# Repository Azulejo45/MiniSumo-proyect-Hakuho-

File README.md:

### ┍━━━━━━━━━━━━»•» 🌺 «•«━━━━┑
#   ┕MiniSumo-Project-Hakuho┙        

### - Proyecto de mini sumo con la capacidad de ser controlado de manera bluetooth y automata. Equipado con 4 sensores:  2 laterales, 1 frontal y uno en la parte inferior, el de piso.
♥

## ..••°°━✦❘༻⋞ 〈 Autores  〉 ⋟༺❘✦━━°°••..

- ⋆ˊˎ-   ┌──༺♥༻❀**Velazquez Joaquim**❀༺♥༻──┐
  
- ⋆ˊˎ-  ↻ ◁ I**Perez Sebastían**I ▷ ↺3:11 ───ㅇ──── 5:25

- ⋆ˊˎ-   》＊•̩̩͙✩•̩̩͙*˚**Demian Ramirez**˚*•̩̩͙✩•̩̩͙*˚《

### *---02/10/2025---*

♥
## •*¨*•.¸¸☆*･ﾟ Especificaciones generales ﾟ･*☆¸¸.•*¨*•

˚₊· ͟͟͞͞➳❥ Dimensiones del robot: 10 cm x 10 cm x 4,5 cm.

˚₊· ͟͟͞͞➳❥ Consumo total: 7,4V.

˚₊· ͟͟͞͞➳❥ Corriente total: 800mA.

˚₊· ͟͟͞͞➳❥ Material de la carrocería: PLA.

˚₊· ͟͟͞͞➳❥ Peso (aproximado): 250g.
## ✭∞∞∞∞∞∞∞∞✭∞∞•,¸,.·' ✩ '·.,¸,•∞∞✭∞∞∞∞∞∞∞∞✭

♥
### ✎  (❁ᴗ͈ˬᴗ͈) ༉‧ ♡*.✧
## Objetivo del proyecto
### ✩°｡𓂃𓏧︶︶︶︶︶︶︶︶┈୨•♡•୧┈︶︶︶︶︶︶︶𓂃𓏧｡°✩
_El objetivo principal de este proyecto es poner a prueba lo aprendido en el transcurso del ciclo educativo y poder aplicarlo en el ensamblaje y preparacion de un robot modelo Mini-Sumo para que se encuentre en condiciones en poder participar en una competencia.
El Mini-sumo está implementado con sensores los cuales lo ayudarán en la detección de obstaculos y/o de un mini-sumo enemigo, utilizando su rampa para contraatacar hasta expulsarlo de la zona de combate._
_Además, el robot consta con un modo "remote control" (RC), esto está implementado con el sistema de bluetooth y wi-fi integrado en el ESP32._
### ✩°｡𓂃𓏧⌒⌒⌒⌒⌒⌒⌒⌒┈୨•♡•୧┈⌒⌒⌒⌒⌒⌒⌒⌒𓂃𓏧｡°✩

♥
### ∘₊✧───∘₊✧───•-•⟮ ◆ ⟯•-•───✧₊∘───✧₊∘
## ˗ˏˋ ꒰ **Este proyecto fue realizado con algunos componentes en donde se puede llegan a encontrar:** ꒱ ˎˊ˗

- Micro: Esp32 S3 super mini.
 > Memoria: 512 KB SRAM, 4 MB Flash.Conectividad: Wi-Fi 802.11 b/g/n (2,4 GHz).\
 > Bluetooth 5.0 LE (Low Energy).\
 > Alimentación: Funciona a 3,3 V con entrada USB-C de 5 V.

- Bateria de Lipo.
 > Almacenamiento: 7,4V.\
 > 2 celdas (3,7V por celda)
  
- Sensor de piso: TCRT5000.
 > Voltaje de operación: 3.3V-5V.\
 > Dimensiones: 31 mm × 13 mm × 2 mm.\
 > Rango de detección: 30° más amplio.

- Sensor detector de obstáculos: AD-32.
 > Voltaje de operacion: 3V-5.5V.\
 > Cantidad de pines: 4.\
 > Distancia de deteccion: 5 a 20mm.
 
- Motores: Micro motores Pololu 250RPM.
 > Dimensiones: 26x10x12mm.\
 > Voltaje de operacion: 6V.\
 > Torque maximo: 333Nm (Newton - metro).

- Puente H: DRV8833.
 > Dimensiones: 4 mm × 18,1 mm × 21,1 mm.\
 > Voltaje de operacion: 2.7V-10.8V.\
 > Corriente máxima de salida: 1,5A.
 ### ∘₊✧───∘₊✧──────✧₊∘───✧₊∘

♥
## ╔══✬✩══╡˚✧Componentes utilizados✧˚╞══✩✬══╗
- ˋ°•*⁀.¸➸ *Esp32 S3 super mini.*
- ˋ°•*⁀.¸➸ *Bateria de Lipo.*
- ˋ°•*⁀.¸➸ *TCRT5000.*
- ˋ°•*⁀.¸➸ *AD-32.*
- ˋ°•*⁀.¸➸ *Micro motores Pololu 250RPM.*
- ˋ°•*⁀.¸➸ *DRV8833.*
## ╚═══*+:｡ . ｡:+*═══✮❁•°❀°•❁✮═══*+:｡ . ｡:+*═══╝
/
/
/
/
/
♥
# Diseño del circuito

## Descripcion del funcionamiento

El minisumo utiliza sus varios sensores para guiarse, con dos ubicados en los costados; otro en la parte frontal. Cuando un objeto entra en el rango del sensor frontal, el minisumo avanza hasta chocar contra dicho objeto. Esto siempre se cumple hasta que se quite la orden.\
Cuando uno de los sensores en los costados detectan algo cerca, se posiciona para estar de frente al objeto, retrocediendo y girando en direccion paralela a este.

♥

## Layout de PCB

# Pasos a seguir para armar el mini-sumo
## ˚*•̩̩͙✩•̩̩͙*˚＊˚*•̩̩͙✩•̩̩͙*˚＊˚*•̩̩͙✩•̩̩͙*˚＊˚*•̩̩͙✩•̩̩͙*˚＊˚*•̩̩͙✩•̩̩͙*˚

### Primero elistaremos las herramientas necesarias para llevar a cabo la placa.
-Un recipiente\
-Percloruro\
-Una agujereadora\
-Una placa de cobre\
-Papel fotografico\
-Tinta Tonel\
-Una impresora(Para imprimir el diseño PCB)
-Cable USB-C (Para cargar el codigo.)

 ### -|preparación de la placa:

1. Descargar el archivo de PCB de "HakuhoNII.kicad_pcb" (YO NO LO DESCARGO PORQUE YA LO TENGO XDDDD).
2. Imprimir el PCB en una hoja fotográfica (como lo son las hojas de revista) con tinta "tonel".
3. Proceda a planchar el PCB a la placa del lado del cobre.
4. Revisar que el diagrama del PCB se haya pegado correctamente retirando la hoja fotográfica y cualquier excendete de esta(Utilice agua para remover con facilidad el papel).
5. Sumergir la placa en un recipiente con percloruro.
6. Dejarlo descansar un tiempo(Resivar periodicamente el cobre de la placa)
7. Cuando el cobre se haya disuelto y solo quede el diseño, retirarlo con CUIDADO(Es un liquido corrosivo;dificil de quitar de la ropa).
8. Limiparlo la placa con agua para quitar el excedente de percloruro.

 ### -|Soldar los componentes en la placa ya hecha en el siguiente orden:
 
1. Puentes
2. Boton
3. Capacitores
4. Switch
5. Pineras
6. Borneras
7. regulador

 ### Medidas de seguridad.

-El percloruro es un tanto corrosivo, capáz de manchar con facilidad la ropa y otra prendas.\
-Cuando vaya a hacer agujeros en la placa, tiene que ser en una superficie solida. Es probable que la placa pueda salir dispara en una base dispareja o inquieta.\
-Mientra planche, este atento a no quemar completamente el papel. Podria causar un incendio.

### Tipo de soldadura/ensamble
Todos los componentes deben fijados a la placa mendiante "soldadura de ola", el cual se utiliza para componentes de orificio pasante(THT). Los componentes debe ser introducidos desde el lado de la placa lisa y sin diseño,para ser soldados en el cobre que se encuentra del otro lado.
En las pineras que estan direccionadas en horizontal, se debe colocar el ESP32(integrado).
En la pineras que se encuentran en vertical, el DRV8833.

### -|Carroceria

1. Descargar el modelo 3D de la carroceria.
2. Descargar un modelo 3D de dos braquets y 2 ruedas con un radio de 20mm.
3. Imprimir ambos archivos.
4. Comprar cuatro tornillos para tuerca M3, 6 tuercas M3 y 2 prisioneros M3.
5. Unir la carroseria con los braquets mediante 4 tornillos M3 y 4 tuercas M3.

### -|Codigo

El codigo establece las instrucciones que ejecutara el integrado para poder accionar y manejar al mini-sumo.\
este es bastante simple y considera los 4 sensores teniendo en cuenta que:

- No debe salir del tatami.
- Debe atacar y empujar al otro mini-sumo fuera del area.
- Esquivar al mini-sumo rival cuando se le de la orden.

#### -|Compilacion/Carga

Cuando la placa ya este monatada, se utilizara un cable USB tipo C para conectar el integrado(ESP32) a un ordenador. Mediante el programa [Arduino IDE](https://www.arduino.cc/en/software). Copie el codigo que se encuentra en este repositorio y pueguelo en el programa. En el apartado superior encontrara 4 botones.\
El primero es para verificar si el programa tiene errores\
El segundo es para subir el codigo al integrado\
El tercero no es importante para esto.\
El cuarto es para poder seleccionar la placa y el puerto\
En este ultimo, busque el siguiente modelo: ESP32_S3_SUPER_MINI, y seleccionelo. En caso de no encontrarlo, use el "ESP32 S3 DEV MODULE". Junto a eso, seleccione el puerto USB por el cual esta conectado a su ordenador(Se cuenta de izquierda a derecha).\
Ahora, verifique el codigo por el primero boton de la parte superior. Si marca algun error, copie el codigo entero de nuevo y vuelva a pegarlo./
Una vez verificada la funcionalidad del codigo, utilice el segundo boton presente para poder subir el codigo al integrado de la placa. Si hay alguno otro error durante este proceso, consulte internet.

#### -[Librerias
Para poner librerias, dirigase al lateral izquierdo de la interfaz de Arduino IDE, y seleccione el tercer boton(Que contiene un simbolo con libros).
En el buscador de esta nueva pagina, encuentre las siguientes librerias:
-AdaFruit_NeoPixel.h

#### -[Datasheets/Referencias
-[AD-32](Recursos/Datasheet AD-32.jpg)

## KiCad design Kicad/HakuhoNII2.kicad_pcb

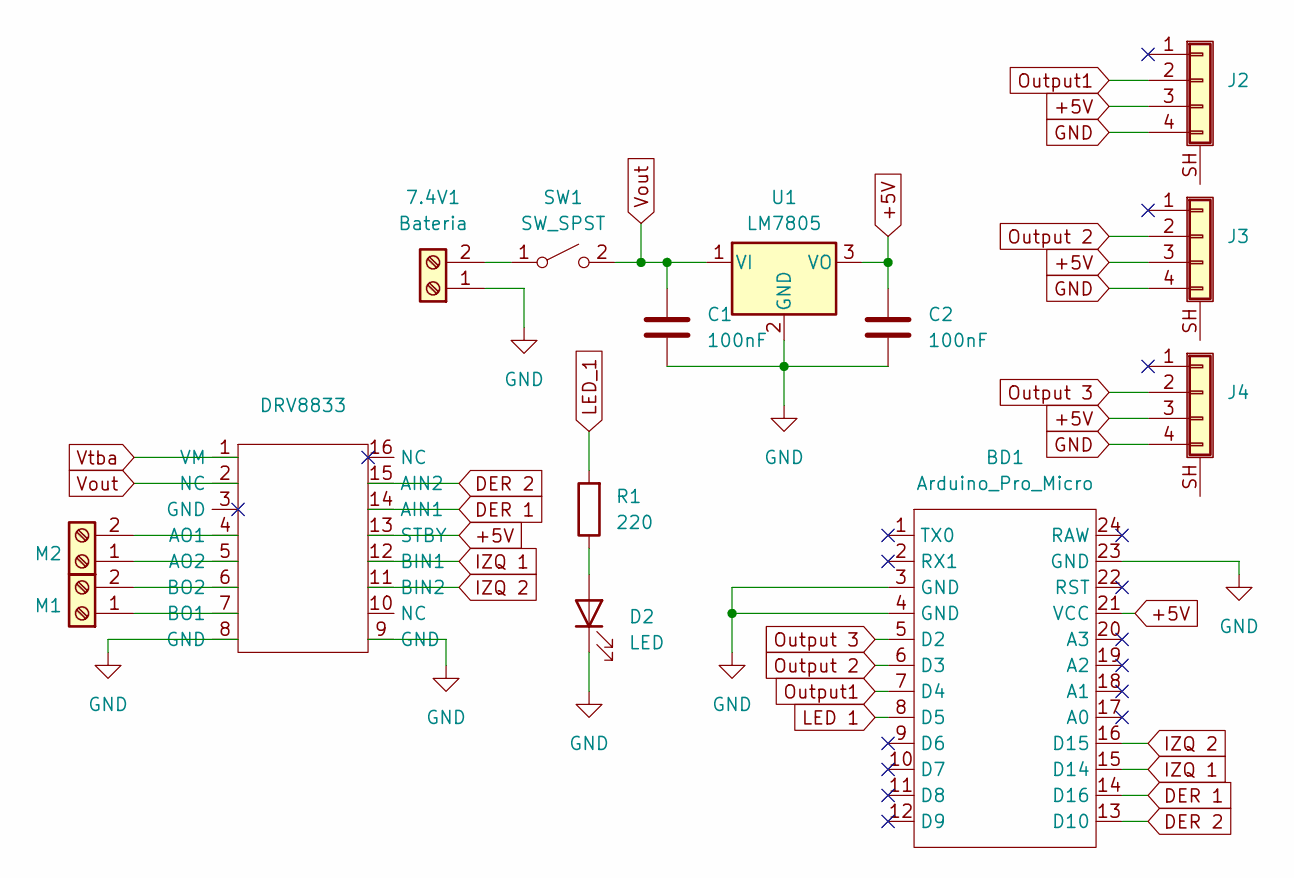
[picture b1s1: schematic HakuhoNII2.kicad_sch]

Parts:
7.4V1: Bateria; TerminalBlock_Phoenix_MKDS-1,5-2-5.08_1x02_P5.08mm_Horizont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
BD1: Arduino_Pro_Micro; Arduino PRO Micro
C1, C2: 100nF; C_Disc_D5.0mm_W2.5mm_P2.50mm
D2: LED; LED_D3.0mm_FlatTop
DRV8833: drv8833
J2, J3, J4: Conn_01x04_Shielded; PinHeader_1x04_P2.54mm_Vertical
M1, M2: Screw_Terminal_01x02; TerminalBlock_Phoenix_MKDS-1,5-2-5.08_1x02_P5.08mm_Horizont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
R1: 220; R_Axial_DIN0207_L6.3mm_D2.5mm_P7.62mm_Horizontal
SW1: SW_SPST; TerminalBlock_Phoenix_MKDS-1,5-2-5.08_1x02_P5.08mm_Horizont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
U1: LM7805; TO-220-3_Vertical

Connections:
+5V: BD1.21 (VCC), C2.1, DRV8833.13 (STBY), J2.3, J3.3, J4.3, U1.3 (VO)
DER 1: BD1.14 (D16), DRV8833.14 (AIN1)
DER 2: BD1.13 (D10), DRV8833.15 (AIN2)
GND: 7.4V1.1, BD1.3 (GND), BD1.4 (GND), BD1.23 (GND), C1.2, C2.2, D2.1 (K), DRV8833.8 (GND), DRV8833.9 (GND), J2.4, J3.4, J4.4, U1.2 (GND)
IZQ 1: BD1.15 (D14), DRV8833.12 (BIN1)
IZQ 2: BD1.16 (D15), DRV8833.11 (BIN2)
LED 1: BD1.8 (D5)
LED_1: R1.2
unnamed: 7.4V1.2, SW1.1 (A)
unnamed: D2.2 (A), R1.1
unnamed: DRV8833.4 (AO1), M2.2
unnamed: DRV8833.5 (AO2), M2.1
unnamed: DRV8833.7 (BO1), M1.1
unnamed: DRV8833.6 (BO2), M1.2
Output1: BD1.7 (D4), J2.2
Output 2: BD1.6 (D3), J3.2
Output 3: BD1.5 (D2), J4.2
Vout: C1.1, DRV8833.2 (NC), SW1.2 (B), U1.1 (VI)
Vtba: DRV8833.1 (VM)

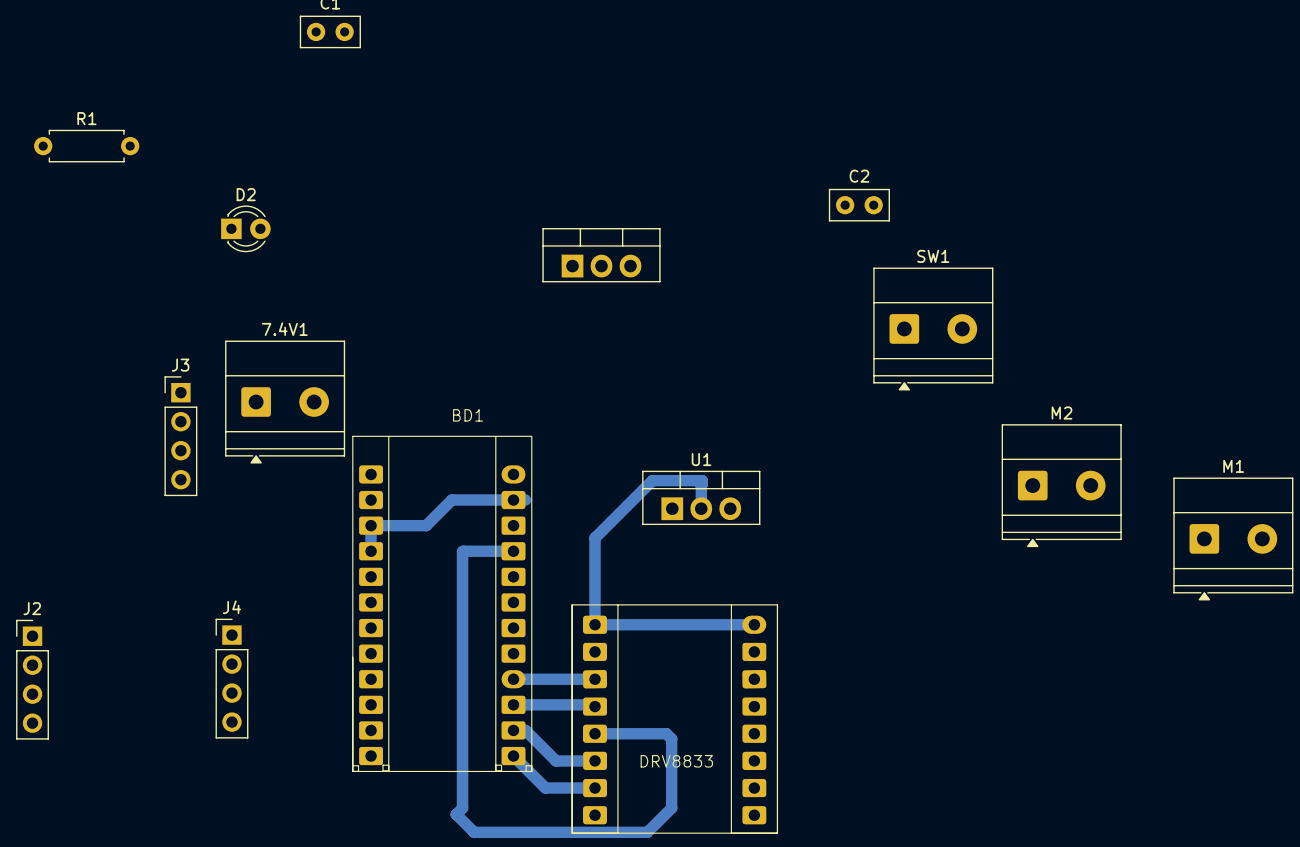
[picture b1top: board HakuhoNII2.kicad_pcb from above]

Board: 2 copper layers, 14 parts (0 on the bottom side), 16 nets.

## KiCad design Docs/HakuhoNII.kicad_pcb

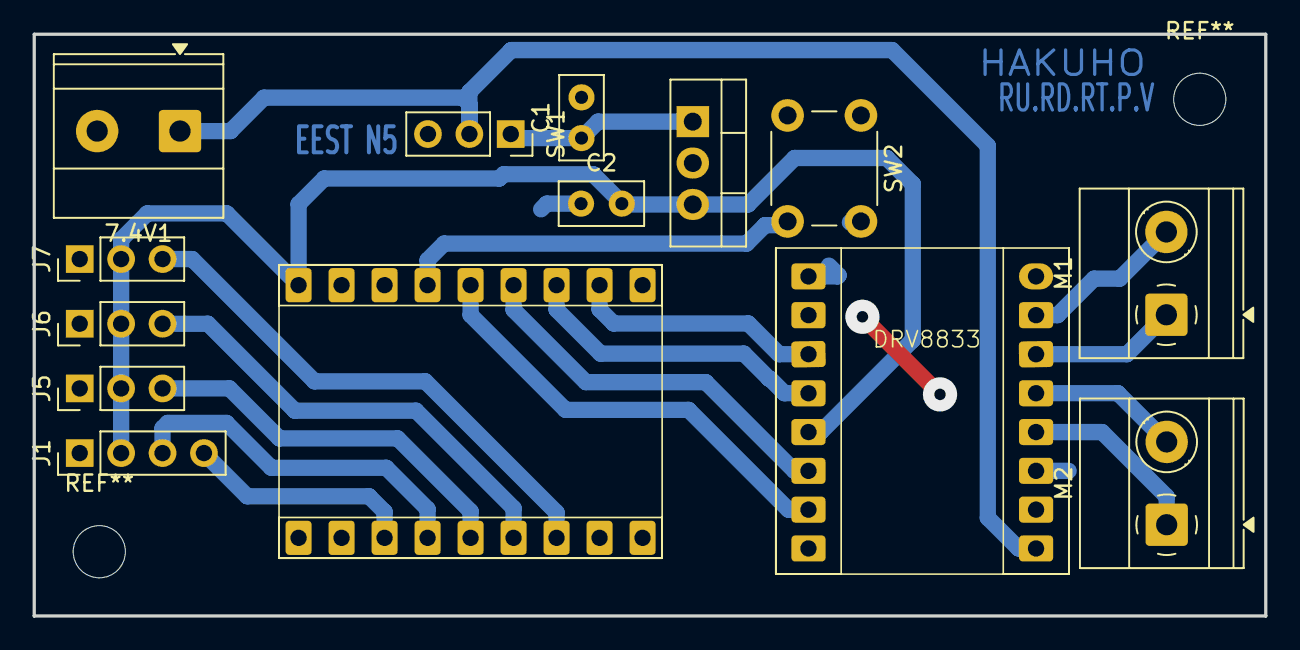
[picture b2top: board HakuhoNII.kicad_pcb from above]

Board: 2 copper layers, 75.5 x 35.7 mm, 14 parts (0 on the bottom side), 18 nets.

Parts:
7.4V1: Bateria; TerminalBlock_Phoenix_MKDS-1,5-2-5.08_1x02_P5.08mm_Horizont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
BD2: ESP32 S3 Super mini; ESP32 S3 SuperMini
C1, C2: 100nF; C_Disc_D5.0mm_W2.5mm_P2.50mm
DRV8833: drv8833
J1: Conn_01x04; PinHeader_1x04_P2.54mm_Vertical
J5, J6, J7: Conn_01x03; PinHeader_1x03_P2.54mm_Vertical
M1, M2: Screw_Terminal_01x02; TerminalBlock_Phoenix_MKDS-1,5-2-5.08_1x02_P5.08mm_Horizont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
SW1: SW_SPST; PinSocket_1x03_P2.54mm_Vertical
SW2: SW_Push_Dual; SW_PUSH_6mm
U1: LM7805; TO-220-3_Vertical

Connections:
+5V: BD2.18 (5V), C2.2, DRV8833.13 (STBY), J1.2, J5.2, J6.2, J7.2, U1.3 (VO)
A0: BD2.4 (2), J1.3
BOTON_1: BD2.15 (13), SW2.2
D0: BD2.3 (1), J1.4
DER 1: BD2.14 (12), DRV8833.15 (AIN2)
DER 2: BD2.13 (11), DRV8833.14 (AIN1)
GND: 7.4V1.2, BD2.17 (GND), C1.2, C2.1, DRV8833.3 (GND), DRV8833.8 (GND), DRV8833.9 (GND), J1.1, J5.1, J6.1, J7.1, SW2.1, U1.2 (GND)
IZQ 1: BD2.12 (10), DRV8833.12 (BIN1)
IZQ 2: BD2.11 (9), DRV8833.11 (BIN2)
unnamed: DRV8833.4 (AO1), M2.1
unnamed: DRV8833.5 (AO2), M2.2
unnamed: DRV8833.7 (BO1), M1.2
unnamed: DRV8833.6 (BO2), M1.1
unnamed: C1.1, SW1.1 (A), U1.1 (VI)
Output1: BD2.5 (3), J5.3
Output 2: BD2.6 (4), J6.3
Output 3: BD2.7 (5), J7.3
Vout: 7.4V1.1, DRV8833.1 (VM), SW1.2 (B)

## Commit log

2025-10-02 README.md
2025-10-09 Create Referencias
2025-10-23 Create codigo_clase_motor_robot
2025-10-23 Rename codigo_clase_motor_robot to codigo_clase_motor_robot.cpp
